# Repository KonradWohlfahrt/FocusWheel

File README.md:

# Focus Wheel 2.0  
**Overview**  
Focus Wheel 2.0 is a compact, standalone focus and time-management device designed to help you stay productive during study sessions or focused work. It combines a clean, minimal design with touch controls, visual feedback, and flexible timer logic, all powered by a rechargeable battery. This second iteration is a major step up from the original Focus Wheel. It introduces battery operation with power-path management, touch-based controls, an integrated LED ring, and a more refined enclosure. The result is a polished desk companion that’s easy to use, highly customizable, and fun to build:  

[Instructables Guide](https://www.instructables.com/Focus-Wheel-20-Your-Next-Gen-Study-Assistant/)  

**Key Features**  
- *Four independent timers*  
Each timer can be configured individually with its own work and break durations. All settings are stored in EEPROM and persist across power cycles.
- *Built-in 20-20 rule*  
Optional eye-break reminders during work sessions help reduce eye strain. The reminder timing can be adjusted in software.
- *Touch-based controls*  
Capacitive touch buttons replace traditional mechanical switches, keeping the design clean and minimal.
- *Rotary encoder interface*  
A rotary encoder is used for intuitive navigation, timer selection, and value adjustments.
- *Integrated LED ring*  
WS2812B LEDs are placed directly on the PCB and provide visual feedback for timers, states, and effects.
- *OLED display*  
A small I2C OLED shows timer status, menus, battery information, and system feedback.
- *Sound and melodies*  
A passive buzzer allows the device to play different tones and melodies for notifications and timer events.
- *Battery powered with USB-C charging*  
The device runs on a LiPo battery and supports simultaneous charging and operation thanks to power-path management.
- *Battery monitoring & protection*  
Battery voltage, charge state, and power source (USB or battery) are monitored in software, with low-voltage shutdown for safety.  

***
# Materials:
| Component | Amount | Silkscreen label |
|:----------|:------:|-----------------:|
| 100n 0603 | 22 | C1,C4,C8,C12,C17,C19,C21-C36 |
| 100p 0805 | 1 | C15 |
| 100r 0805 | 2 | R9,R12 |
| 100u 1206 | 1 | C20 |
| 10k 0805 | 8 | R6,R11,R13,R18-R21,R28 |
| 10u 0805 | 5 | C3,C9,C11,C14,C16 |
| 15k 0805 | 1 | R15 |
| 1k 0805 | 4 | R7,R8,R10,R27 |
| 1k5 0805 | 1 | R4 |
| 1N4001 SMA | 1 | D3 |
| 1u 0805 | 3 | C2,C5,C18 |
| 2.2uH APH0420 | 1 | L1 |
| 309k 0805 | 1 | R17 |
| 330r 0805 | 1 | R24 |
| 33k 0805 | 1 | R25 |
| 39k 0805 | 1 | R3 |
| 3k9 0805 | 1 | R5 |
| 4.7u 0805 | 4 | C6,C7,C10,C13 |
| 4.7uH ANR3015 | 1 | L2 |
| 47k 0805 | 1 | R26 |
| 4k7 0805 | 2 | R22,R23 |
| 5k1 0805 | 2 | R1,R2 |
| 68k 0805 | 1 | R14 |
| 976k 0805 | 1 | R16 |
| AO3400A SOT-23 | 1 | Q3 |
| BQ24075RGT | 1 | U2 |
| Buzzer MLT-7525 | 1 | BZ1 |
| JST PH2.00mm 2P Horizontal | 1 | J2 |
| DW01A SOT-23-6 | 1 | U3 |
| ESP32-C3-WROOM-02 | 1 | U7 |
| FS8205A SOT-23-6 | 1 | Q1 |
| IRLML6402 SOT-23 | 1 | Q2 |
| LED 3.0mm | 2 | D1,D2 |
| MCP1640Cx-xCHY SOT-23-6 | 1 | U6 |
| MMBT2222A SOT-23 | 1 | Q4 |
| OLED I2C 0.91" | 1 | U10 |
| Rotary Encoder | 1 | SW1 |
| SN74LV1T34DBV SOT-23-5 | 1 | U11 |
| SS34 SMA | 1 | D20 |
| TLV62569DBV SOT-23-5 | 1 | U5 |
| TTP223 Touch Module | 3 | U4,U8,U9 |
| USB-C 16P | 1 | J1 |
| USBLC6-2SC6 SOT-23-6 | 1 | U1 |
| WS2812B 5050 | 16 | D4-D19 |
| Custom PCB | 1 | - |
| 3D printed housing | 1 | - |
| 303450 500mAh LiPo battery | 1 | - |
| M3 3x4.5mm threaded heat inserts | 6 | - |
| M3x4mm screw | 2 | - |
| M3x10mm screw | 4 | - |

***
# Schematic & PCB:
_Schematic of the Focus Wheel V2.1_

_Lables for soldering components_

***
# Programming
Programmed with the Arduino IDE and ESP32 board manager. Install the following libraries:
- [DonutStudioTimer](https://github.com/KonradWohlfahrt/Arduino-Timer-Library)
- [RotaryEncoder](https://github.com/mathertel/RotaryEncoder)
- [FastLED](https://github.com/FastLED/FastLED)
- [U8g2](https://github.com/olikraus/u8g2)

**Uploading:**  
Board: `ESP32C3 Dev Module`\
Settings:
```cpp
USB CDC On Boot: "Enabled" <- to make USB Serial work  
CPU Frequency: "160MHz (WiFi)"  
Core Debug Level: "None"  
Erase All Flash Before Sketch Upload: "Disabled"  
Flash Frequency: "80MHz"  
Flash Mode: "QIO"  
Flash Size: "4MB (32Mb)"  
JTAG Adapter: "Disabled"  
Partition Scheme: "Default 4MB with spiffs (1.2MB APP/1.5MB SPIFFS)"  
Upload Speed: "921600"  
Zigbee Mode: "Disabled"  
Programmer: "Esptool"  
```
Connection via USB-C.\
Press the knob button (Flash) when powering up the device for the first time.

***
# 3D Printing
Print `FocusWheel_Bottom` and `FocusWheel_Top` - depending on what components you would like to use. Finally, print `Knob`. Put in the six threaded heat inserts and screw everything together. The knob slides on top.

***
# Functions
The following button functions are used:
- bottom button: enable/disable sound
- middle button: start timer, pause timer, change selection (rotation)
- top button: skip timers, enter/exit settings

**Customization & Hacking**  
All firmware is written for the Arduino ecosystem, and the code is intended to be easy to extend and experiment with. This project is fully open to customization. You can:
- Modify timer logic and behaviors
- Change LED effects and animations
- Add or replace melodies
- Adjust UI flow and menu structure

**Final Notes**  
Focus Wheel 2.0 is meant to be both a useful productivity tool and an enjoyable electronics project. Whether you build it as-is or use it as a base for your own ideas, feel free to experiment, improve, and make it your own. If you build one, I’d love to see it—share your version and ideas!

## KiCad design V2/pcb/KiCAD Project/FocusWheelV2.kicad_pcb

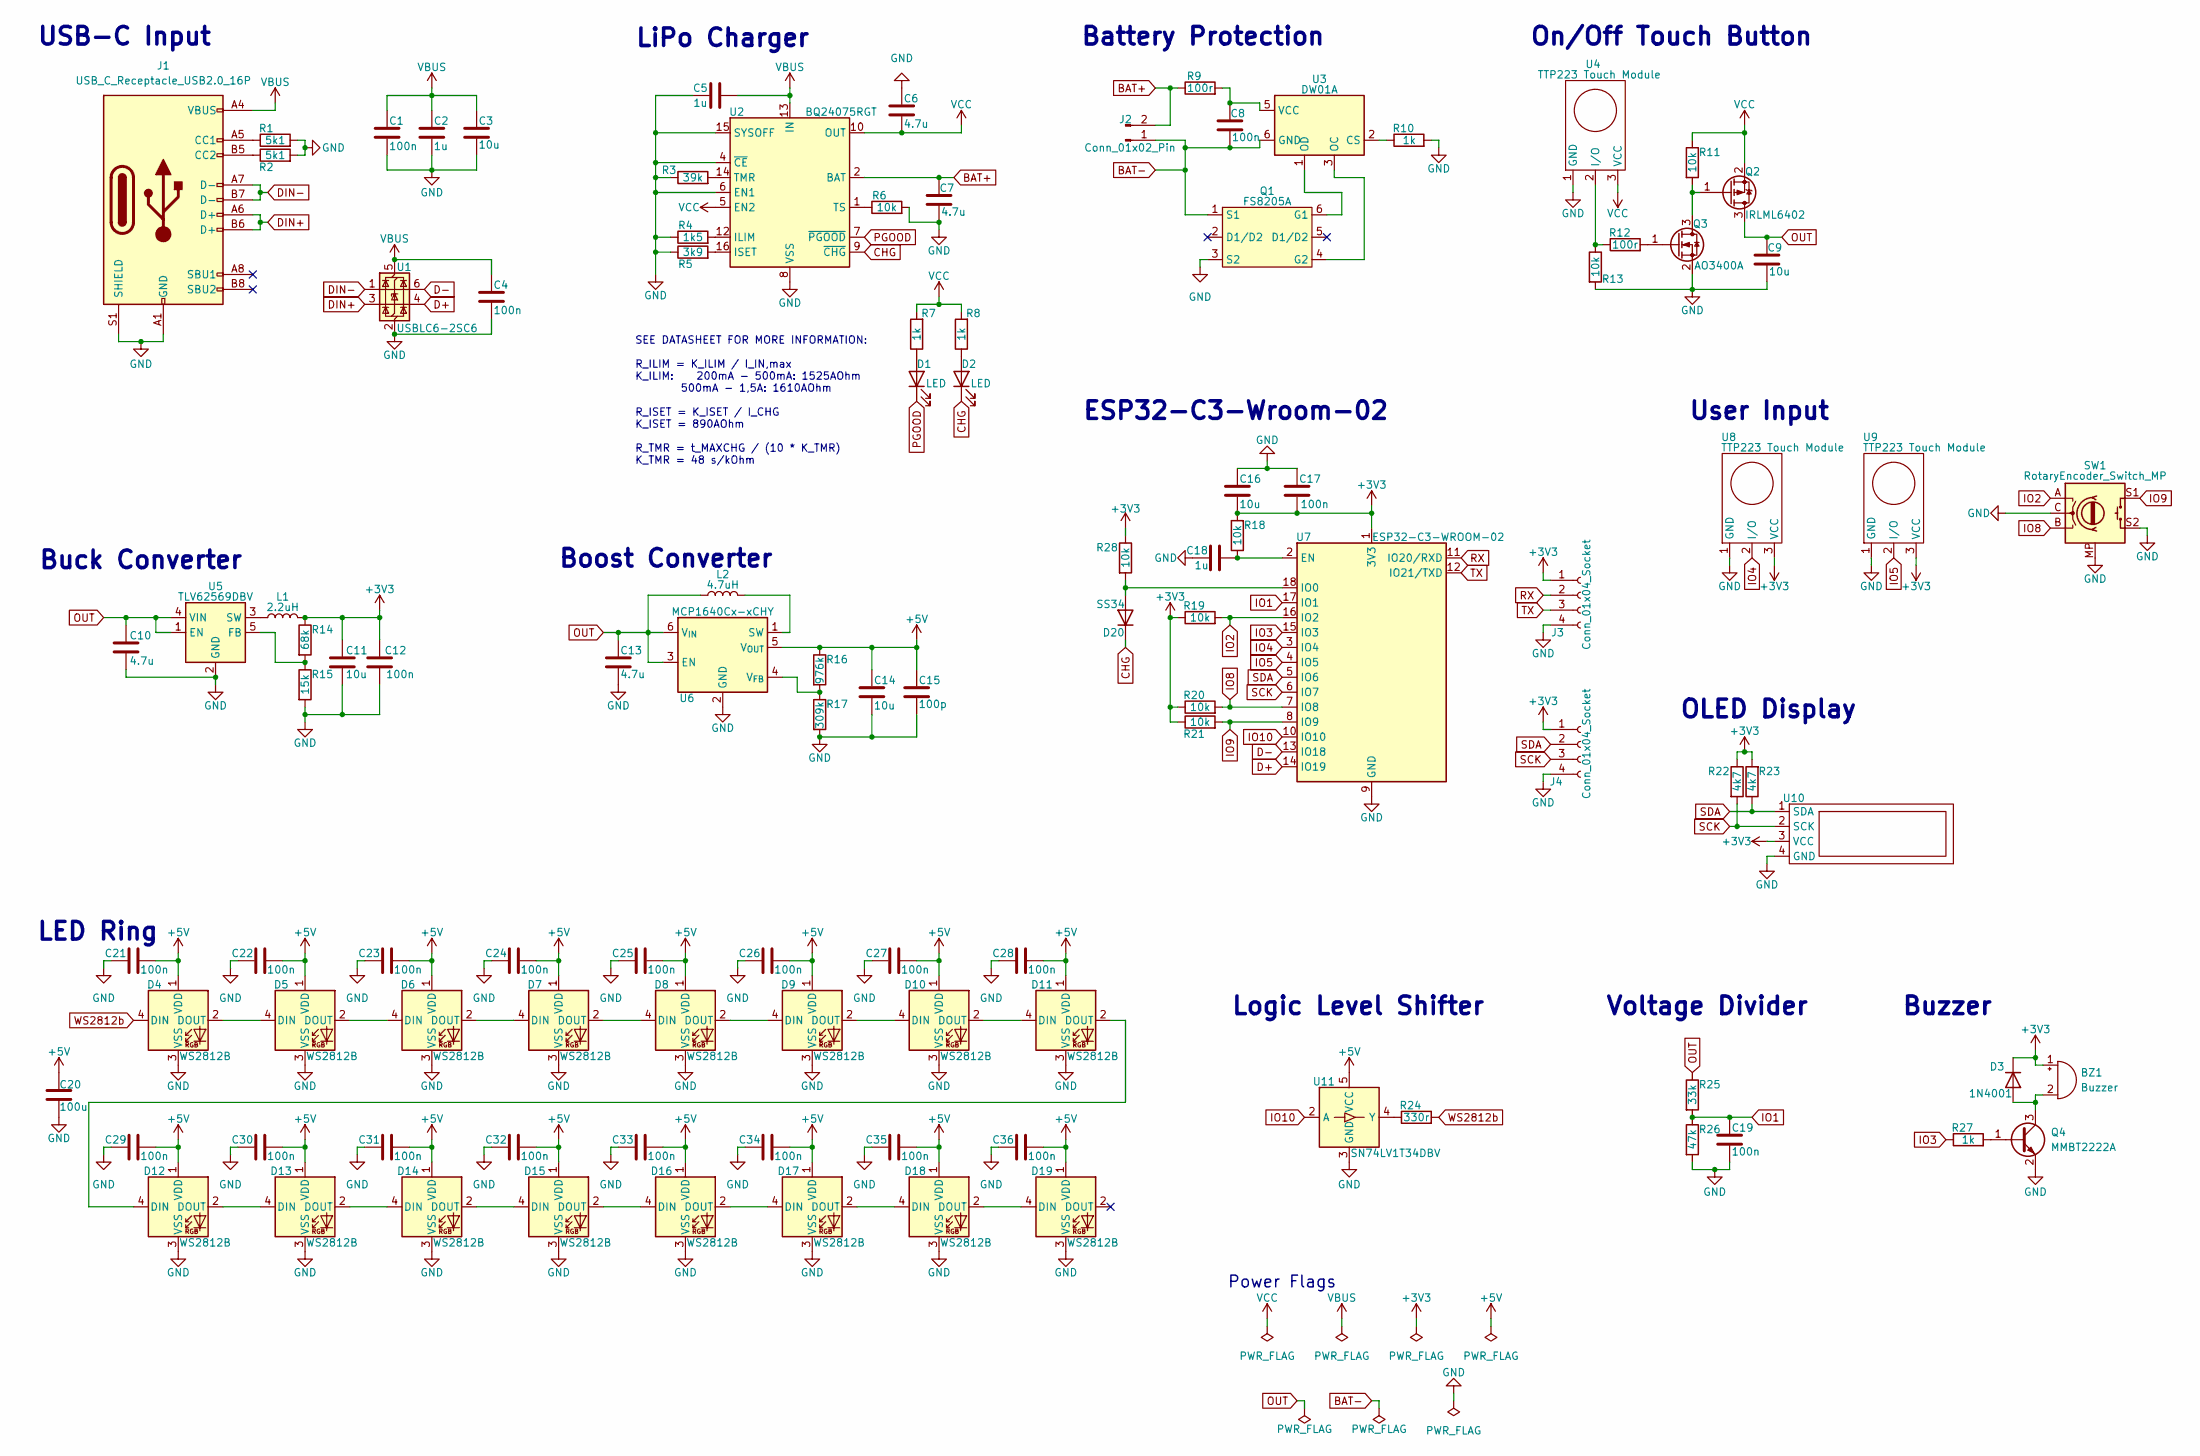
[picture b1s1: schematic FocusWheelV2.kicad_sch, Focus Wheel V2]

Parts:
BZ1: Buzzer; Huaneng MLT-7525
C1, C4, C8, C12, C17, C19, C21, C22, C23, C24, C25, C26, C27, C28, C29, C30, C31, C32, C33, C34, C35, C36: 100n; C_0603_1608Metric
C2, C5, C18: 1u; C_0805_2012Metric
C3, C9, C11, C14, C16: 10u; C_0805_2012Metric
C6, C7, C10, C13: 4.7u; C_0805_2012Metric
C15: 100p; C_0805_2012Metric
C20: 100u; C_1206_3216Metric
D1, D2: LED; LED_D3.0mm_Horizontal_O1.27mm_Z2.0mm
D3: 1N4001; D_SMA
D4, D5, D6, D7, D8, D9, D10, D11, D12, D13, D14, D15, D16, D17, D18, D19: WS2812B; LED_WS2812B_PLCC4_5.0x5.0mm_P3.2mm
D20: SS34; D_SMA
J1: USB_C_Receptacle_USB2.0_16P; USB_C_Receptacle_HCTL_HC-TYPE-C-16P-01A
J2: Conn_01x02_Pin; JST_PH_S2B-PH-K_1x02_P2.00mm_Horizontal
J3, J4: Conn_01x04_Socket; PinHeader_1x04_P2.54mm_Vertical
L1: 2.2uH; L_APV_APH0420
L2: 4.7uH; L_APV_ANR3015
Q1: FS8205A; SOT-23-6
Q2: IRLML6402; SOT-23
Q3: AO3400A; SOT-23
Q4: MMBT2222A; SOT-23
R1, R2: 5k1; R_0805_2012Metric
R3: 39k; R_0805_2012Metric
R4: 1k5; R_0805_2012Metric
R5: 3k9; R_0805_2012Metric
R6, R11, R13, R18, R19, R20, R21, R28: 10k; R_0805_2012Metric
R7, R8, R10, R27: 1k; R_0805_2012Metric
R9, R12: 100r; R_0805_2012Metric
R14: 68k; R_0805_2012Metric
R15: 15k; R_0805_2012Metric
R16: 976k; R_0805_2012Metric
R17: 309k; R_0805_2012Metric
R22, R23: 4k7; R_0805_2012Metric
R24: 330r; R_0805_2012Metric
R25: 33k; R_0805_2012Metric
R26: 47k; R_0805_2012Metric
SW1: RotaryEncoder_Switch_MP; RotaryEncoder_Alps_EC11E-Switch_Vertical_H20mm
U1: USBLC6-2SC6; SOT-23-6
U2: BQ24075RGT; VQFN-16-1EP_3x3mm_P0.5mm_EP1.6x1.6mm
U3: DW01A; SOT-23-6
U4, U8, U9: TTP223 Touch Module
U5: TLV62569DBV; SOT-23-5
U6: MCP1640Cx-xCHY; SOT-23-6
U7: ESP32-C3-WROOM-02
U10: OLED I2C 0.91"; OLED I2C 0.91
U11: SN74LV1T34DBV; SOT-23-5

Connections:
+3V3: BZ1.1 (+), C11.1, C12.1, C16.2, C17.2, D3.1 (K), J3.1, J4.1, L1.2, R14.1, R18.2, R19.1, R20.1, R21.1, R22.1, R23.2, R28.1, U7.1 (3V3), U8.3 (VCC), U9.3 (VCC), U10.3 (VCC)
+5V: C14.1, C15.1, C20.1, C21.2, C22.2, C23.2, C24.2, C25.2, C26.2, C27.2, C28.2, C29.2, C30.2, C31.2, C32.2, C33.2, C34.2, C35.2, C36.2, D4.1 (VDD), D5.1 (VDD), D6.1 (VDD), D7.1 (VDD), D8.1 (VDD), D9.1 (VDD), D10.1 (VDD), D11.1 (VDD), D12.1 (VDD), D13.1 (VDD), D14.1 (VDD), D15.1 (VDD), D16.1 (VDD), D17.1 (VDD), D18.1 (VDD), D19.1 (VDD), R16.1, U6.5 (V_{OUT}), U11.5 (VCC)
BAT+: C7.1, J2.2, R9.1, U2.2 (BAT), U2.3 (BAT)
BAT-: C8.2, J2.1, Q1.1 (S1), U3.6 (GND)
CHG: D2.1 (K), D20.1 (K), U2.9 (~CHG)
D+: U1.4 (I/O2), U7.14 (IO19)
D-: U1.6 (I/O1), U7.13 (IO18)
DIN+: J1.A6 (D+), J1.B6 (D+), U1.3 (I/O2)
DIN-: J1.A7 (D-), J1.B7 (D-), U1.1 (I/O1)
GND: C1.1, C2.2, C3.2, C4.1, C5.1, C6.1, C7.2, C9.2, C10.2, C11.2, C12.2, C13.2, C14.2, C15.2, C16.1, C17.1, C18.1, C19.2, C20.2, C21.1, C22.1, C23.1, C24.1, C25.1, C26.1, C27.1, C28.1, C29.1, C30.1, C31.1, C32.1, C33.1, C34.1, C35.1, C36.1, D4.3 (VSS), D5.3 (VSS), D6.3 (VSS), D7.3 (VSS), D8.3 (VSS), D9.3 (VSS), D10.3 (VSS), D11.3 (VSS), D12.3 (VSS), D13.3 (VSS), D14.3 (VSS), D15.3 (VSS), D16.3 (VSS), D17.3 (VSS), D18.3 (VSS), D19.3 (VSS), J1.A1 (GND), J1.A12 (GND), J1.B1 (GND), J1.B12 (GND), J1.S1 (SHIELD), J3.4, J4.4, Q1.3 (S2), Q3.2 (S), Q4.2 (E), R1.2, R2.2, R3.1, R4.1, R5.1, R6.2, R10.2, R13.2, R15.2, R17.2, R26.2, SW1.C, SW1.MP, SW1.S2, U1.2 (GND), U2.4 (~CE), U2.6 (EN1), U2.8 (VSS), U2.15 (SYSOFF), U2.17 (VSS), U4.1 (GND), U5.2 (GND), U6.2 (GND), U7.9 (GND), U7.19 (GND), U8.1 (GND), U9.1 (GND), U10.4 (GND), U11.3 (GND)
IO1: C19.1, R25.2, R26.1, U7.17 (IO1)
IO2: R19.2, SW1.A, U7.16 (IO2)
IO3: R27.1, U7.15 (IO3)
IO4: U7.3 (IO4), U8.2 (I/O)
IO5: U7.4 (IO5), U9.2 (I/O)
IO8: R20.2, SW1.B, U7.7 (IO8)
IO9: R21.2, SW1.S1, U7.8 (IO9)
IO10: U7.10 (IO10), U11.2 (A)
unnamed: BZ1.2 (-), D3.2 (A), Q4.3 (C)
unnamed: D1.2 (A), R7.1
unnamed: D2.2 (A), R8.1
unnamed: D4.2 (DOUT), D5.4 (DIN)
unnamed: D5.2 (DOUT), D6.4 (DIN)
unnamed: D6.2 (DOUT), D7.4 (DIN)
unnamed: D7.2 (DOUT), D8.4 (DIN)
unnamed: D8.2 (DOUT), D9.4 (DIN)
unnamed: D9.2 (DOUT), D10.4 (DIN)
unnamed: D10.2 (DOUT), D11.4 (DIN)
unnamed: D11.2 (DOUT), D12.4 (DIN)
unnamed: D12.2 (DOUT), D13.4 (DIN)
unnamed: D13.2 (DOUT), D14.4 (DIN)
unnamed: D14.2 (DOUT), D15.4 (DIN)
unnamed: D15.2 (DOUT), D16.4 (DIN)
unnamed: D16.2 (DOUT), D17.4 (DIN)
unnamed: D17.2 (DOUT), D18.4 (DIN)
unnamed: D18.2 (DOUT), D19.4 (DIN)
unnamed: D20.2 (A), R28.2, U7.18 (IO0)
unnamed: J1.A5 (CC1), R1.1
unnamed: J1.B5 (CC2), R2.1
unnamed: Q1.6 (G1), U3.1 (OD)
unnamed: Q1.4 (G2), U3.3 (OC)
unnamed: Q2.1 (G), Q3.3 (D), R11.2
unnamed: Q3.1 (G), R12.2
unnamed: Q4.1 (B), R27.2
unnamed: R4.2, U2.12 (ILIM)
unnamed: R5.2, U2.16 (ISET)
unnamed: R3.2, U2.14 (TMR)
unnamed: R6.1, U2.1 (TS)
unnamed: R10.1, U3.2 (CS)
unnamed: C8.1, R9.2, U3.5 (VCC)
unnamed: R12.1, R13.1, U4.2 (I/O)
unnamed: R14.2, R15.1, U5.5 (FB)
unnamed: L1.1, U5.3 (SW)
unnamed: L2.2, U6.1 (SW)
unnamed: R16.2, R17.1, U6.4 (V_{FB})
unnamed: C18.2, R18.1, U7.2 (EN)
unnamed: R24.1, U11.4 (Y)
OUT: C9.1, C10.1, C13.1, L2.1, Q2.3 (D), R25.1, U5.1 (EN), U5.4 (VIN), U6.3 (EN), U6.6 (V_{IN})
PGOOD: D1.1 (K), U2.7 (~PGOOD)
RX: J3.2, U7.11 (IO20/RXD)
SCK: J4.3, R22.2, U7.6 (IO7), U10.2 (SCK)
SDA: J4.2, R23.1, U7.5 (IO6), U10.1 (SDA)
TX: J3.3, U7.12 (IO21/TXD)
VBUS: C1.2, C2.1, C3.1, C4.2, C5.2, J1.A4 (VBUS), J1.A9 (VBUS), J1.B4 (VBUS), J1.B9 (VBUS), U1.5 (VBUS), U2.13 (IN)
VCC: C6.2, Q2.2 (S), R7.2, R8.2, R11.1, U2.5 (EN2), U2.10 (OUT), U2.11 (OUT), U4.3 (VCC)
WS2812b: D4.4 (DIN), R24.2

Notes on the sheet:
ESP32-C3-Wroom-02
User Input
SEE DATASHEET FOR MORE INFORMATION: R_ILIM = K_ILIM / I_IN,max K_ILIM: 200mA - 500mA: 1525AOhm 500mA - 1,5A: 1610AOhm R_ISET = K_ISET / I_CHG K_ISET = 890AOhm R_TMR = t_MAXCHG / (10 * K_TMR) K_TMR = 48 s/kOhm
Boost Converter
Battery Protection
Logic Level Shifter
On/Off Touch Button
LED Ring
OLED Display
Buck Converter
Voltage Divider
LiPo Charger
Power Flags
Buzzer
USB-C Input

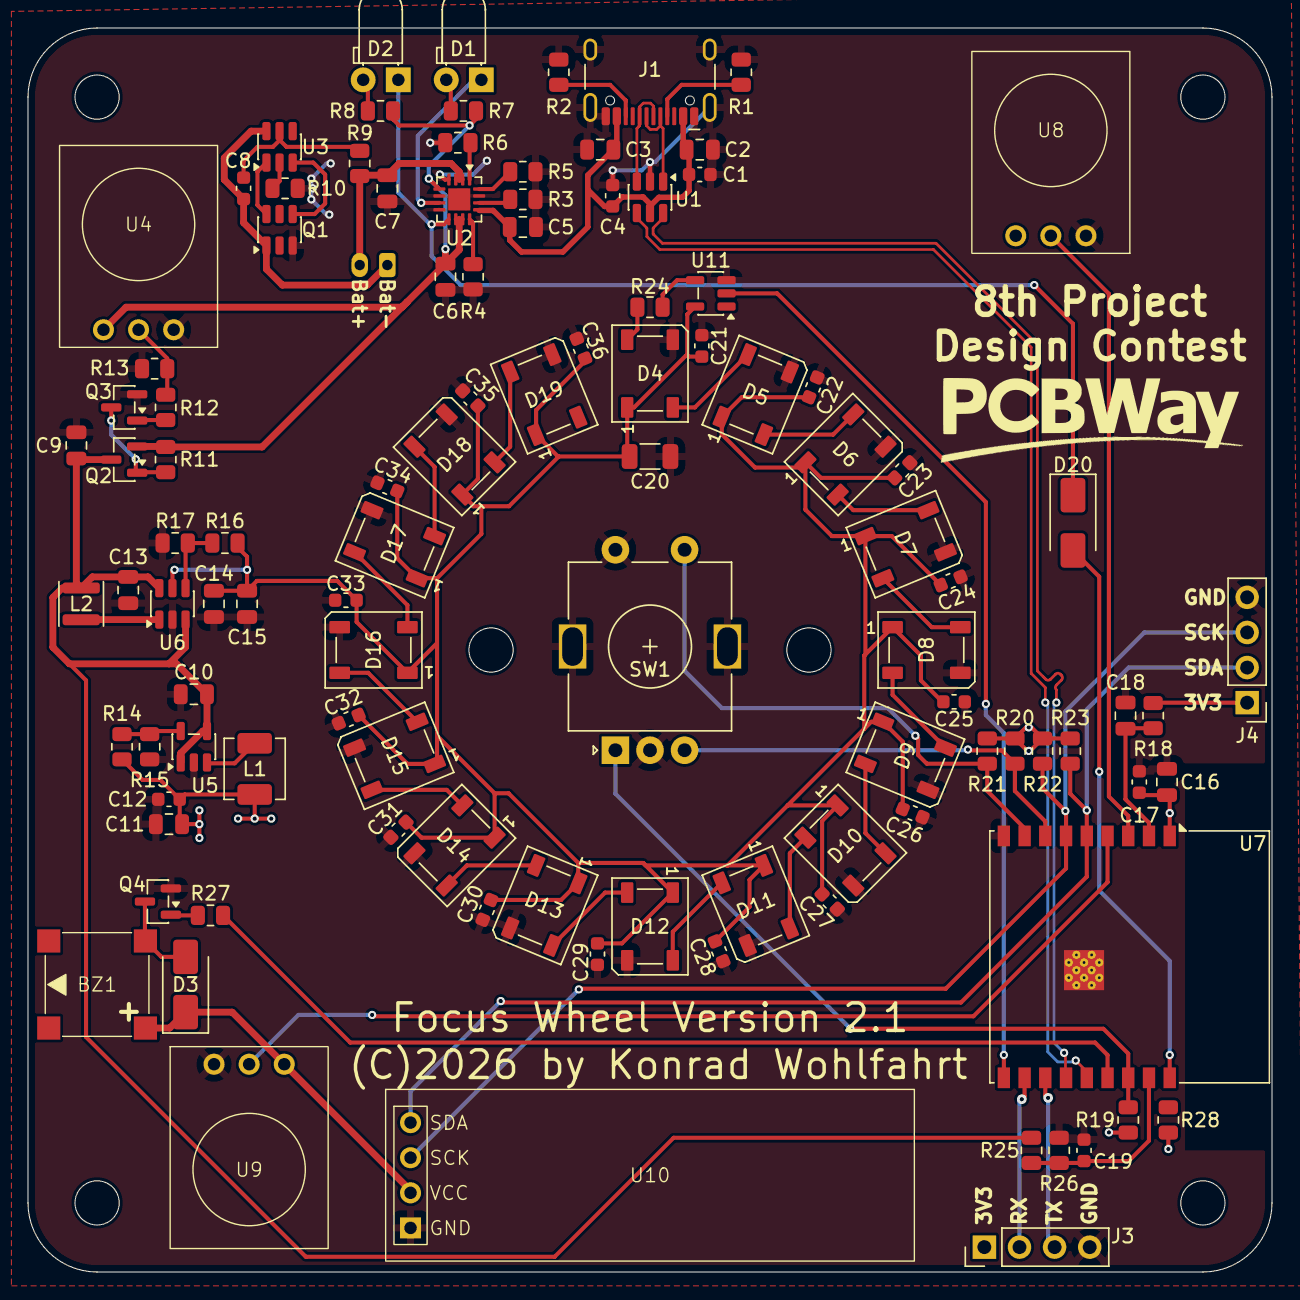
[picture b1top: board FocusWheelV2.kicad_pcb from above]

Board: 2 copper layers, 90.0 x 90.0 mm, 107 parts (1 on the bottom side), 66 nets.

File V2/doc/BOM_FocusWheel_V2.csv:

"Reference","Qty","Value","DNP","Exclude from BOM","Exclude from Board","Footprint","Datasheet"
"BZ1","1","Buzzer","","","","KonradsLibrary:Huaneng MLT-7525","~"
"C1,C4,C8,C12,C17,C19,C21,C22,C23,C24,C25,C26,C27,C28,C29,C30,C31,C32,C33,C34,C35,C36","22","100n","","","","Capacitor_SMD:C_0603_1608Metric","~"
"C2,C5,C18","3","1u","","","","Capacitor_SMD:C_0805_2012Metric","~"
"C3,C9,C11,C14,C16","5","10u","","","","Capacitor_SMD:C_0805_2012Metric","~"
"C6,C7,C10,C13","4","4.7u","","","","Capacitor_SMD:C_0805_2012Metric","~"
"C15","1","100p","","","","Capacitor_SMD:C_0805_2012Metric","~"
"C20","1","100u","","","","Capacitor_SMD:C_1206_3216Metric","~"
"D1,D2","2","LED","","","","LED_THT:LED_D3.0mm_Horizontal_O1.27mm_Z2.0mm","~"
"D3","1","1N4001","","","","Diode_SMD:D_SMA","~"
"D4,D5,D6,D7,D8,D9,D10,D11,D12,D13,D14,D15,D16,D17,D18,D19","16","WS2812B","","","","LED_SMD:LED_WS2812B_PLCC4_5.0x5.0mm_P3.2mm","https://cdn-shop.adafruit.com/datasheets/WS2812B.pdf"
"J1","1","USB_C_Receptacle_USB2.0_16P","","","","Connector_USB:USB_C_Receptacle_HCTL_HC-TYPE-C-16P-01A","https://www.usb.org/sites/default/files/documents/usb_type-c.zip"
"J2","1","Conn_01x02_Pin","","","","Connector_JST:JST_PH_S2B-PH-K_1x02_P2.00mm_Horizontal","~"
"J3,J4","2","Conn_01x04_Socket","","","","Connector_PinHeader_2.54mm:PinHeader_1x04_P2.54mm_Vertical","~"
"L1","1","2.2uH","","","","Inductor_SMD:L_APV_APH0420","~"
"L2","1","4.7uH","","","","Inductor_SMD:L_APV_ANR3015","~"
"Q1","1","FS8205A","","","","Package_TO_SOT_SMD:SOT-23-6",""
"Q2","1","IRLML6402","","","","Package_TO_SOT_SMD:SOT-23","https://www.infineon.com/dgdl/irlml6402pbf.pdf?fileId=5546d4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"
"Q3","1","AO3400A","","","","Package_TO_SOT_SMD:SOT-23","http://www.aosmd.com/pdfs/datasheet/AO3400A.pdf"
"Q4","1","MMBT2222A","","","","Package_TO_SOT_SMD:SOT-23","https://assets.nexperia.com/documents/data-sheet/MMBT2222A.pdf"
"R1,R2","2","5k1","","","","Resistor_SMD:R_0805_2012Metric","~"
"R3","1","39k","","","","Resistor_SMD:R_0805_2012Metric","~"
"R4","1","1k5","","","","Resistor_SMD:R_0805_2012Metric","~"
"R5","1","3k9","","","","Resistor_SMD:R_0805_2012Metric","~"
"R6,R11,R13,R18,R19,R20,R21","7","10k","","","","Resistor_SMD:R_0805_2012Metric","~"
"R7,R8,R10,R27","4","1k","","","","Resistor_SMD:R_0805_2012Metric","~"
"R9,R12","2","100r","","","","Resistor_SMD:R_0805_2012Metric","~"
"R14","1","68k","","","","Resistor_SMD:R_0805_2012Metric","~"
"R15","1","15k","","","","Resistor_SMD:R_0805_2012Metric","~"
"R16","1","976k","","","","Resistor_SMD:R_0805_2012Metric","~"
"R17","1","309k","","","","Resistor_SMD:R_0805_2012Metric","~"
"R22,R23","2","4k7","","","","Resistor_SMD:R_0805_2012Metric","~"
"R24","1","330r","","","","Resistor_SMD:R_0805_2012Metric","~"
"R25","1","33k","","","","Resistor_SMD:R_0805_2012Metric","~"
"R26","1","47k","","","","Resistor_SMD:R_0805_2012Metric","~"
"SW1","1","RotaryEncoder_Switch_MP","","","","Rotary_Encoder:RotaryEncoder_Alps_EC11E-Switch_Vertical_H20mm","~"
"U1","1","USBLC6-2SC6","","","","Package_TO_SOT_SMD:SOT-23-6","https://www.st.com/resource/en/datasheet/usblc6-2.pdf"
"U2","1","BQ24075RGT","","","","Package_DFN_QFN:VQFN-16-1EP_3x3mm_P0.5mm_EP1.6x1.6mm","http://www.ti.com/lit/ds/symlink/bq24075.pdf"
"U3","1","DW01A","","","","Package_TO_SOT_SMD:SOT-23-6","https://hmsemi.com/downfile/DW01A.PDF"
"U4,U8,U9","3","TTP223 Touch Module","","","","KonradsLibrary:TTP223 Touch Module",""
"U5","1","TLV62569DBV","","","","Package_TO_SOT_SMD:SOT-23-5","http://www.ti.com/lit/ds/symlink/tlv62569.pdf"
"U6","1","MCP1640Cx-xCHY","","","","Package_TO_SOT_SMD:SOT-23-6","http://ww1.microchip.com/downloads/en/DeviceDoc/20002234D.pdf"
"U7","1","ESP32-C3-WROOM-02","","","","RF_Module:ESP32-C3-WROOM-02","https://www.espressif.com/sites/default/files/documentation/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"
"U10","1","OLED I2C 0.91""","","","","KonradsLibrary:OLED I2C 0.91",""
"U11","1","SN74LV1T34DBV","","","","Package_TO_SOT_SMD:SOT-23-5","https://www.ti.com/lit/ds/symlink/sn74lv1t34.pdf"

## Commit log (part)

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2025-08-06 update knob stl
2026-01-26 Added Focus Wheel Version 2

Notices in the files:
V2/pcb/KiCAD Project/FocusWheelV2.kicad_pcb:
(C)2026 by Konrad Wohlfahrt
